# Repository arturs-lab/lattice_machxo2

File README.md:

# lattice_machxo2
lattice machxo2 256 breakout board

## Power Supply
All four VIO circuits are connected to 3V3 by traces on bottom of the board. 
In this configuration you do not have to populate VIO jumpers, voltaage regulator nor its capacitors.
If you want to use different VIO, cut corresponding trace(s), install jumper(s) and 
VIO voltage regulator and caps.

The 1Ohm resistors on the bottom of the board can be used to measure current draw of IO sections by 
measuring voltage drop on resistors. 0Ohm jumpers can also be installed.

## Oscillator
To use on-board oscillator, install it and jumper pin OSC to CLK.
To use off-board clock source, connect it between CLK and GND pins. 
In this case on-board oscillator does not have to be installed.

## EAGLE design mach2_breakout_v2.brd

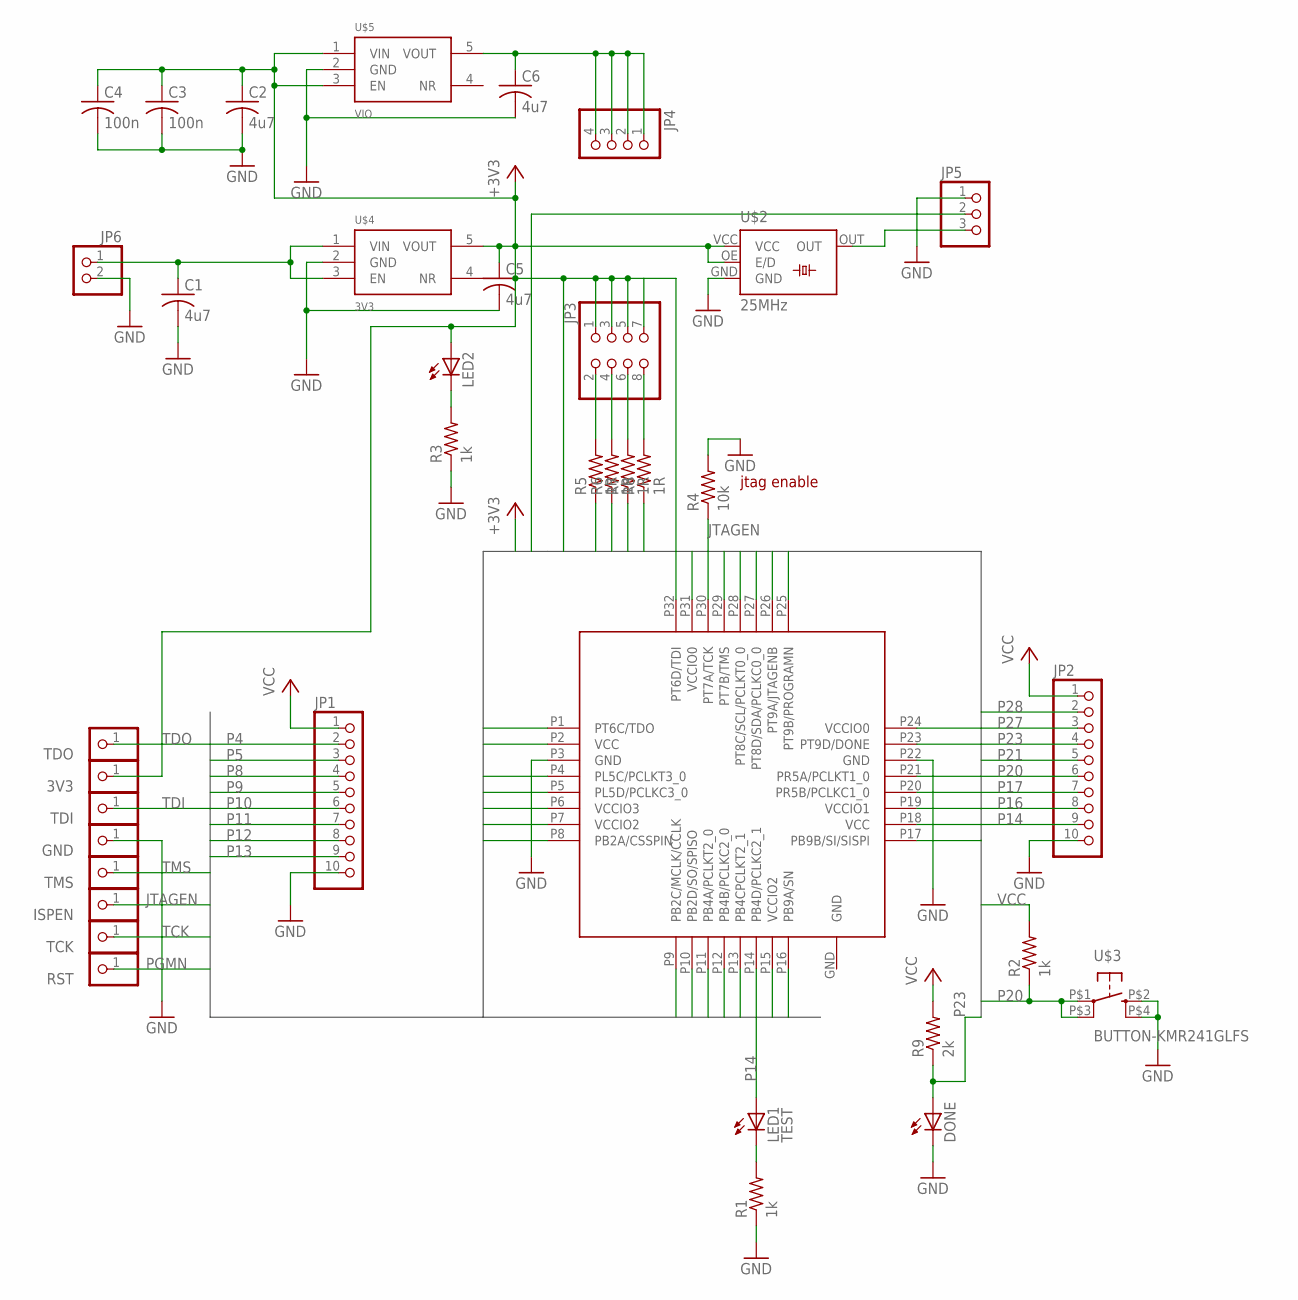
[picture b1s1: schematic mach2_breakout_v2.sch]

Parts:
3V3: PINHD-1X1; 1X01
C1, C2, C5, C6: 4u7; C0603
C3, C4: 100n; C0603
DONE: LEDCHIPLED_0603; CHIPLED_0603
GND: PINHD-1X1; 1X01
ISPEN: PINHD-1X1; 1X01
JP1, JP2: PINHD-1X10; 1X10
JP3: PINHD-2X4V; 2X04
JP4: PINHD-1X4; 1X04
JP5: PINHD-1X3; 1X03
JP6: PINHD-1X2; 1X02
LED1: TEST; CHIPLED_0603
LED2: LEDCHIPLED_0603; CHIPLED_0603
R1, R2, R3: 1k; R0603
R4: 10k; R0603
R5, R6, R7, R8: 1R; R0805
R9: 2k; R0603
RST: PINHD-1X1; 1X01
TCK: PINHD-1X1; 1X01
TDI: PINHD-1X1; 1X01
TDO: PINHD-1X1; 1X01
TMS: PINHD-1X1; 1X01
U$1: XO2-256; QFN32
U$2: 25MHz; FXO_3225
U$3: BUTTON-KMR241GLFS; PUSHBUTTON-KMR241GLFS
U$4: 3V3; SOT23-5
U$5: VIO; SOT23-5

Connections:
GND: C1.2, C2.2, C3.2, C4.2, C5.2, C6.2, DONE.C, GND.1, JP1.10, JP2.10, JP5.1, JP6.2, R1.1, R3.1, R4.2, U$1.P3 (GND), U$1.P22 (GND), U$2.GND, U$3.P$2 (2), U$3.P$4 (4), U$4.2 (GND), U$5.2 (GND)
JTAGEN: ISPEN.1, R4.1, U$1.P26 (PT9A/JTAGENB)
unnamed: C1.1, JP6.1, U$4.1 (VIN), U$4.3 (EN)
unnamed: JP5.3, U$2.OUT
unnamed: LED1.C, R1.2
unnamed: JP3.8, R8.2
unnamed: LED2.C, R3.2
unnamed: C6.1, JP4.1, JP4.2, JP4.3, JP4.4, U$5.5 (VOUT)
unnamed: JP3.6, R7.2
unnamed: JP3.4, R6.2
unnamed: JP3.2, R5.2
P4: JP1.2, JP5.2, U$1.P4 (PL5C/PCLKT3_0)
P5: JP1.3, U$1.P5 (PL5D/PCLKC3_0)
P8: JP1.4, U$1.P8 (PB2A/CSSPIN)
P9: JP1.5, U$1.P9 (PB2C/MCLK/CCLK)
P10: JP1.6, U$1.P10 (PB2D/SO/SPISO)
P11: JP1.7, U$1.P11 (PB4A/PCLKT2_0)
P12: JP1.8, U$1.P12 (PB4B/PCLKC2_0)
P13: JP1.9, U$1.P13 (PB4CPCLKT2_1)
P14: JP2.9, LED1.A, U$1.P14 (PB4D/PCLKC2_1)
P16: JP2.8, U$1.P16 (PB9A/SN)
P17: JP2.7, U$1.P17 (PB9B/SI/SISPI)
P20: JP2.6, R2.1, U$1.P20 (PR5B/PCLKC1_0), U$3.P$1 (1), U$3.P$3 (3)
P21: JP2.5, U$1.P21 (PR5A/PCLKT1_0)
P23: DONE.A, JP2.4, R9.1, U$1.P23 (PT9D/DONE)
P27: JP2.3, U$1.P27 (PT8D/SDA/PCLKC0_0)
P28: JP2.2, U$1.P28 (PT8C/SCL/PCLKT0_0)
PGMN: RST.1, U$1.P25 (PT9B/PROGRAMN)
TCK: TCK.1, U$1.P30 (PT7A/TCK)
TDI: TDI.1, U$1.P32 (PT6D/TDI)
TDO: TDO.1, U$1.P1 (PT6C/TDO)
TMS: TMS.1, U$1.P29 (PT7B/TMS)
VCC: 3V3.1, C2.1, C3.1, C4.1, C5.1, JP1.1, JP2.1, JP3.1, JP3.3, JP3.5, JP3.7, LED2.A, R2.2, R9.2, U$1.P2 (VCC), U$1.P18 (VCC), U$2.OE (E/D), U$2.VCC, U$4.5 (VOUT), U$5.1 (VIN), U$5.3 (EN)
VCCIO0: R5.1, U$1.P24 (VCCIO0), U$1.P31 (VCCIO0)
VCCIO1: R6.1, U$1.P19 (VCCIO1)
VCCIO2: R7.1, U$1.P7 (VCCIO2), U$1.P15 (VCCIO2)
VCCIO3: R8.1, U$1.P6 (VCCIO3)

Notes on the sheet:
jtag enable

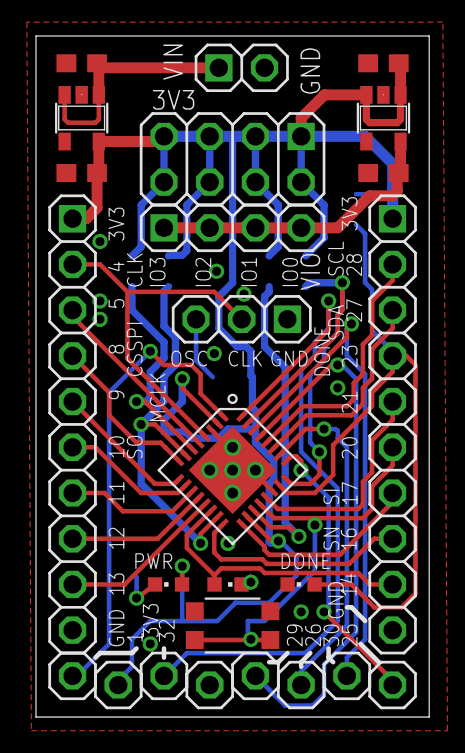
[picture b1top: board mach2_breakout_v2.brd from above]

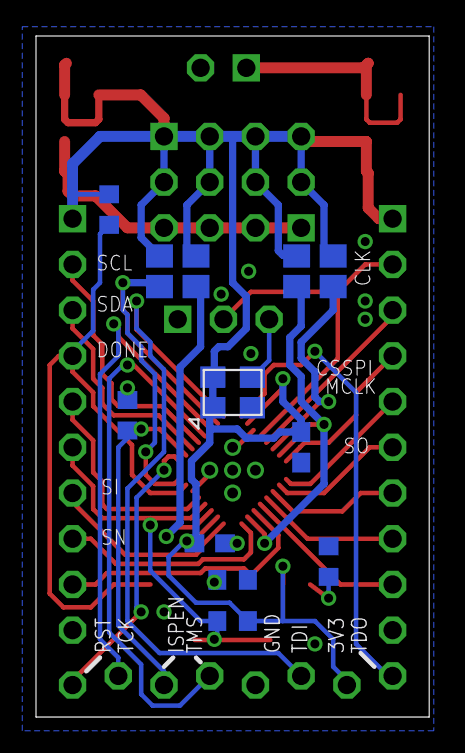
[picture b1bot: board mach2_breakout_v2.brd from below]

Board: 2 copper layers, 21.8 x 37.8 mm, 37 parts (12 on the bottom side), 37 nets.

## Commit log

2025-06-16 add board image
2025-06-16 add details to README.md
